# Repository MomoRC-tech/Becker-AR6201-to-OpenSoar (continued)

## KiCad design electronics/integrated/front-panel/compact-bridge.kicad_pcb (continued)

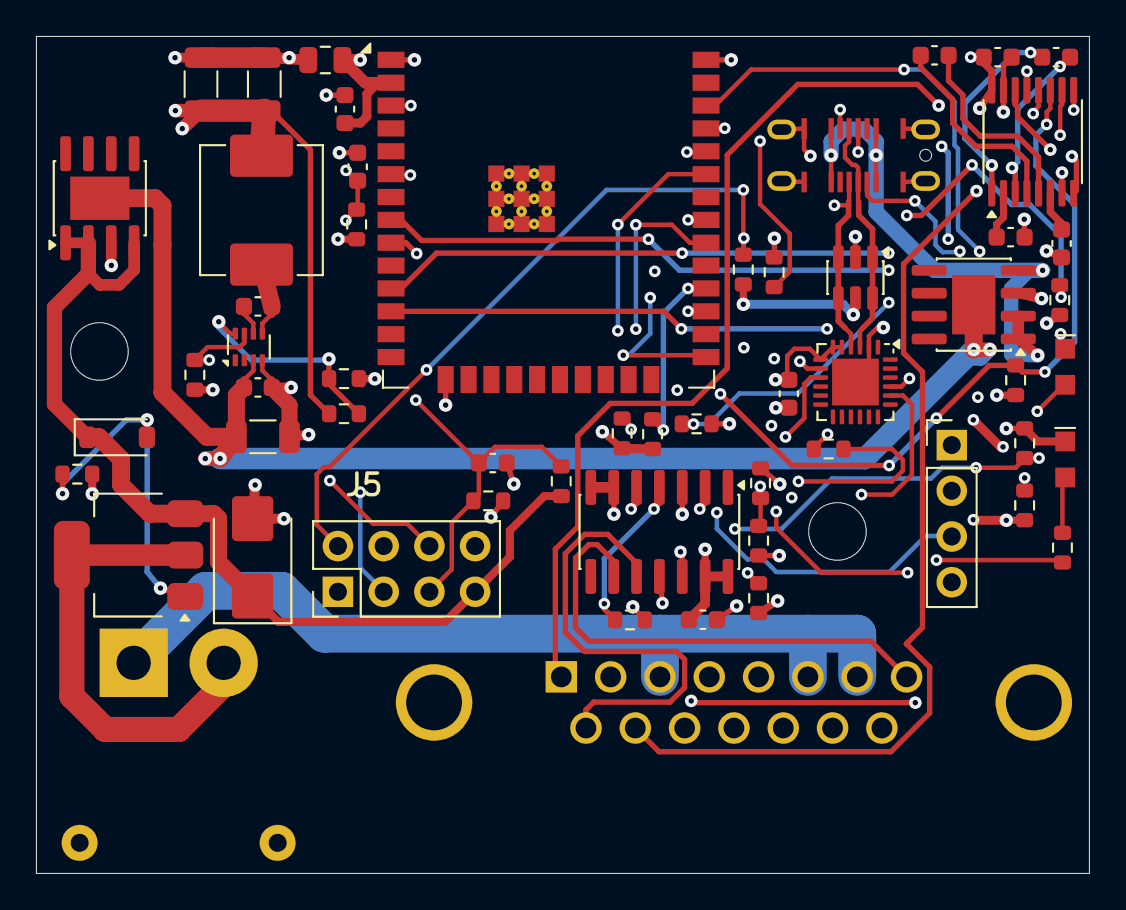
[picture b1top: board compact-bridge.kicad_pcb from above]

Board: 4 copper layers, 58.5 x 46.5 mm, 59 parts (0 on the bottom side), 50 nets.

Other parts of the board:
H1, H2: M3; MountingHole_3.2mm_M3

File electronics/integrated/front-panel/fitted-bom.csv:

Fitted references,Value,Orderable MPN,JLCPCB SKU,Footprint,Process,JLC tier,Qty per board,Qty for 10,USD per piece,USD per board,USD for 10,Stock 2026-11-21,JLCPCB link
U1,ESP32-WROOM-32E-H4,ESP32-WROOM-32E-H4,C3013935,ESP32-WROOM-32E-Edge,SMT,Extended,1,10,3.9086,3.9086,39.0860,2953,https://jlcpcb.com/partdetail/C3013935
J1,DA-15 male,D15P33E4GV00LF,C3139986,Amphenol_D15P33E4GV00LF,Wave,Extended,1,10,1.8275,1.8275,18.2750,572,https://jlcpcb.com/partdetail/C3139986
J4,USB4145-03-0230-C,USB4145-03-0230-C,C5291559,GCT_USB4145,SMT,Extended,1,10,1.1338,1.1338,11.3380,422,https://jlcpcb.com/partdetail/C5291559
U8,CH9102F,CH9102F,C2858418,QFN-24-1EP_4x4mm_P0.5mm_EP2.6x2.6mm,SMT,Extended,1,10,1.0259,1.0259,10.2590,13582,https://jlcpcb.com/partdetail/C2858418
"U6, U7",MX5050S6030A1,MX5050S6030A1,C54800033,SOIC-8-1EP_3.9x4.9mm_P1.27mm_EP2.41x3.3mm,SMT,Extended,2,20,0.4042,0.8084,8.0840,2774,https://jlcpcb.com/partdetail/C54800033
Q1,DMP6023LE-13,DMP6023LE-13,C154901,SOT-223-3_TabPin2,SMT,Extended,1,10,0.7854,0.7854,7.8540,2701,https://jlcpcb.com/partdetail/C154901
U4,TPS62933PDRLR,TPS62933PDRLR,C5219254,SOT-583-8,SMT,Extended,1,10,0.6757,0.6757,6.7570,5766,https://jlcpcb.com/partdetail/C5219254
U3,SIT3491EESD,SIT3491EESD,C496617,SOIC-14_3.9x8.7mm_P1.27mm,SMT,Extended,1,10,0.4303,0.4303,4.3030,3462,https://jlcpcb.com/partdetail/C496617
J2,XT30PW-M,XT30PW-M30.G.Y,C431092,AMASS_XT30PW-M,Wave,Extended,1,10,0.3354,0.3354,3.3540,94579,https://jlcpcb.com/partdetail/C431092
U2,SP3232EEY-L/TR,SP3232EEY-L/TR,C13482,TSSOP-16_4.4x5mm_P0.65mm,SMT,Basic,1,10,0.3163,0.3163,3.1630,216181,https://jlcpcb.com/partdetail/C13482
"C14, C15",22uF 25V,CL31A226KAHNNNE,C12891,C_1206_3216Metric,SMT,Basic,2,20,0.1028,0.2056,2.0560,2572259,https://jlcpcb.com/partdetail/C12891
D3,USBLC6-2SC6,USBLC6-2SC6,C7519,SOT-23-6,SMT,Extended,1,10,0.1561,0.1561,1.5610,43431,https://jlcpcb.com/partdetail/C7519
D2,SMBJ16A,SMBJ16A,C151254,D_SMB,SMT,Extended,1,10,0.1347,0.1347,1.3470,2227,https://jlcpcb.com/partdetail/C151254
C12,10uF 50V,CL31A106KBHNNNE,C13585,C_1206_3216Metric,SMT,Basic,1,10,0.1226,0.1226,1.2260,4049915,https://jlcpcb.com/partdetail/C13585
L1,4.7uH,MWSA0603S-4R7MT,C408447,L_Sunlord_MWSA0603S,SMT,Extended,1,10,0.1098,0.1098,1.0980,17380,https://jlcpcb.com/partdetail/C408447
"C3, C4, C5, C6, C7, C8, C9, C10, C13, C18",100nF,CC0603KRX7R9BB104,C14663,C_0603_1608Metric,SMT,Basic,10,100,0.0056,0.0560,0.5600,53169882,https://jlcpcb.com/partdetail/C14663
"C1, C26",1uF,CC0603KRX7R8BB105,C106858,C_0603_1608Metric,SMT,Extended,2,20,0.0180,0.0360,0.3600,243689,https://jlcpcb.com/partdetail/C106858
D5,Red side-view,LTST-S270KRKT,C125114,LiteOn_LTST-S270,SMT,Extended,1,10,0.0320,0.0320,0.3200,34030,https://jlcpcb.com/partdetail/C125114
C2,10uF,CL21A106KAYNNNE,C15850,C_0805_2012Metric,SMT,Basic,1,10,0.0311,0.0311,0.3110,8807078,https://jlcpcb.com/partdetail/C15850
D4,Green side-view,LTST-S270KGKT,C125113,LiteOn_LTST-S270,SMT,Extended,1,10,0.0288,0.0288,0.2880,1825,https://jlcpcb.com/partdetail/C125113
D1,BZT52C12,BZT52C12,C19077410,D_SOD-123,SMT,Extended,1,10,0.0169,0.0169,0.1690,313228,https://jlcpcb.com/partdetail/C19077410
"R4, R15, R17, R18, R21, R22, R23",1k,0603WAF1001T5E,C21190,R_0603_1608Metric,SMT,Basic,7,70,0.0016,0.0112,0.1120,40604954,https://jlcpcb.com/partdetail/C21190
"R1, R2, R9, R11, R24, R25",10k,0603WAF1002T5E,C25804,R_0603_1608Metric,SMT,Basic,6,60,0.0017,0.0102,0.1020,42620670,https://jlcpcb.com/partdetail/C25804
"R5, R8, R10",100k,0603WAF1003T5E,C25803,R_0603_1608Metric,SMT,Basic,3,30,0.0029,0.0087,0.0870,13049045,https://jlcpcb.com/partdetail/C25803
"R3, R13, R14",4.7k,0603WAF4701T5E,C23162,R_0603_1608Metric,SMT,Basic,3,30,0.0028,0.0084,0.0840,19323654,https://jlcpcb.com/partdetail/C23162
R6,75k,0603WAF7502T5E,C23242,R_0603_1608Metric,SMT,Basic,1,10,0.0021,0.0021,0.0210,628647,https://jlcpcb.com/partdetail/C23242
R7,24k,0603WAF2402T5E,C23352,R_0603_1608Metric,SMT,Basic,1,10,0.0019,0.0019,0.0190,662659,https://jlcpcb.com/partdetail/C23352
